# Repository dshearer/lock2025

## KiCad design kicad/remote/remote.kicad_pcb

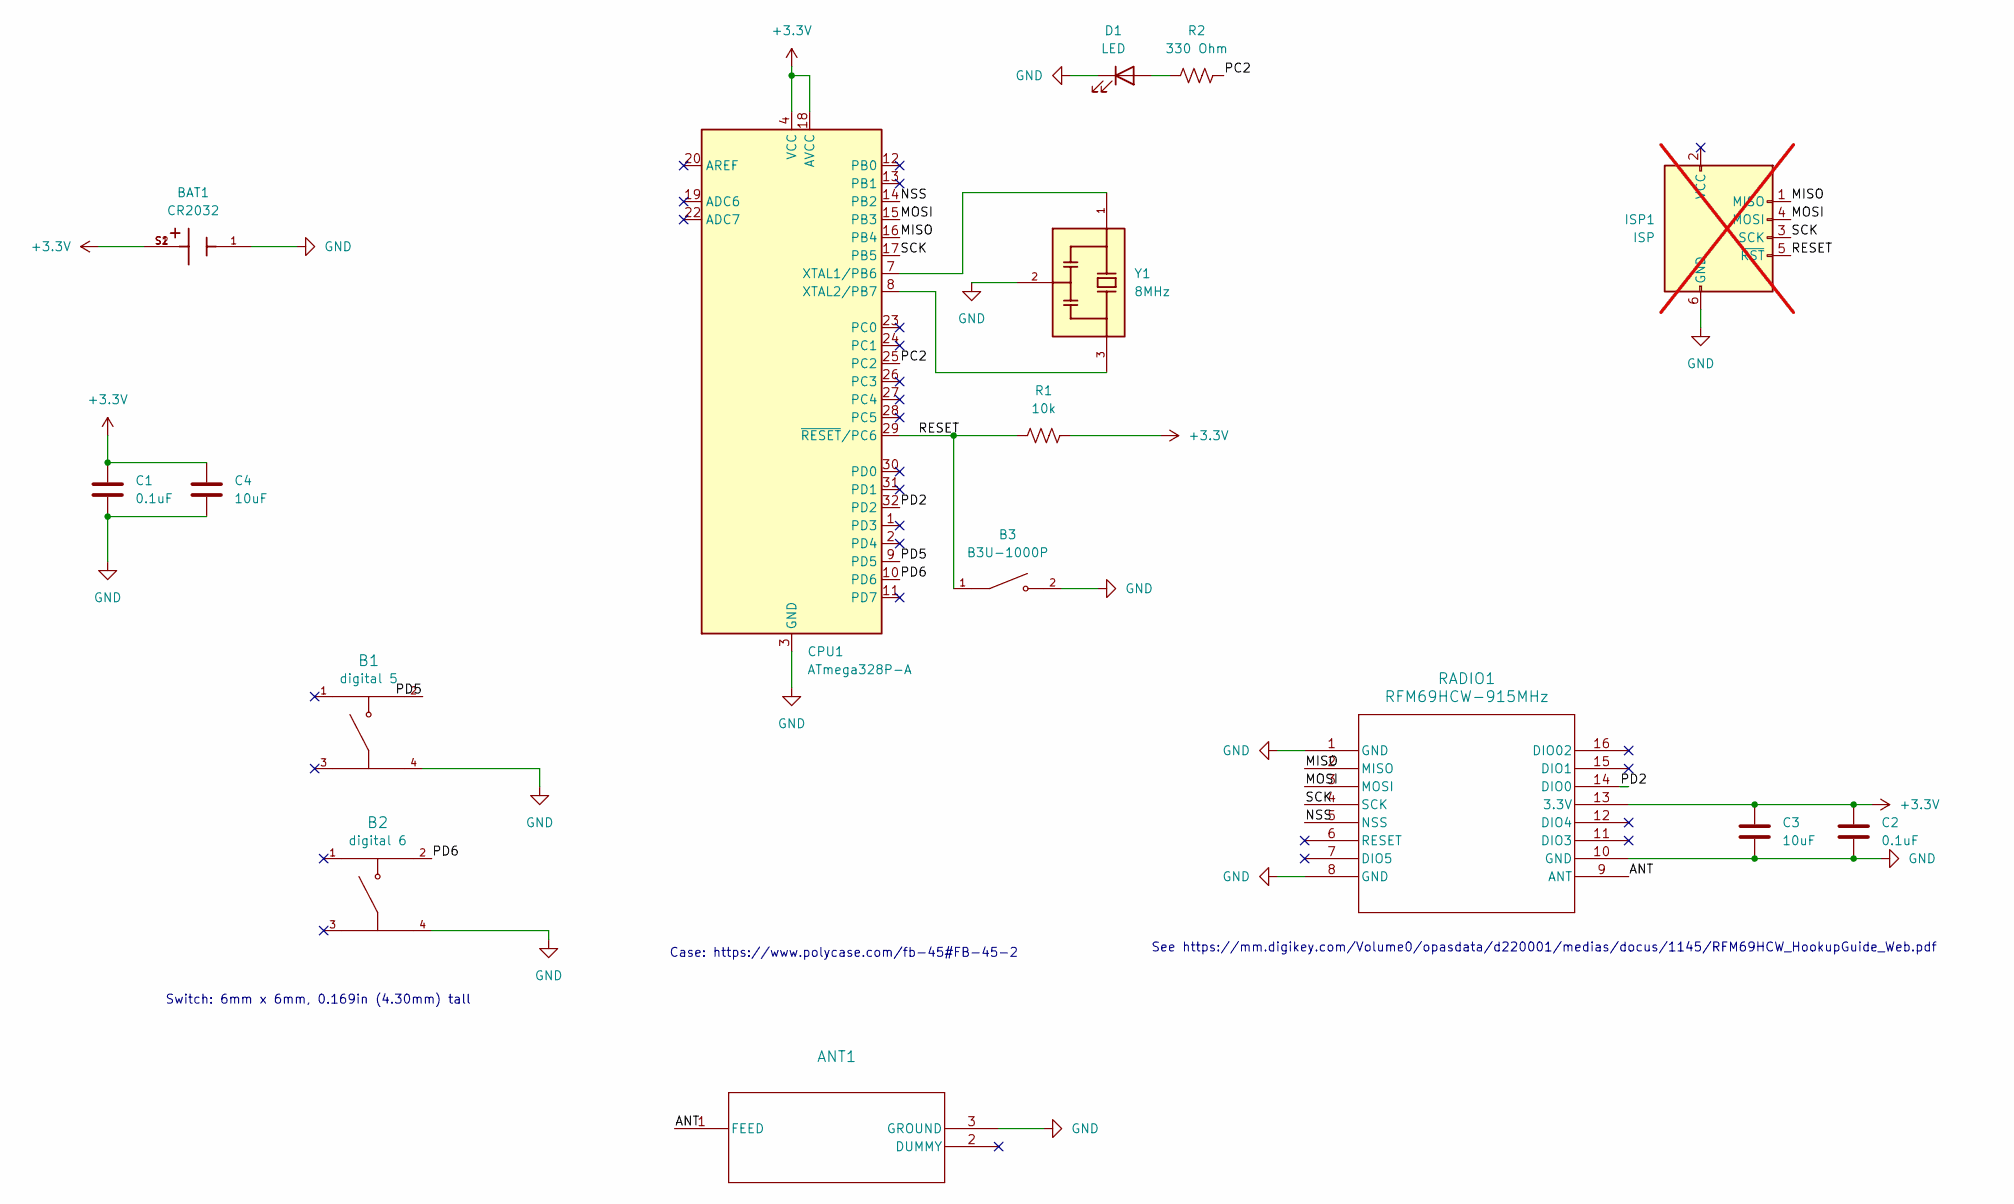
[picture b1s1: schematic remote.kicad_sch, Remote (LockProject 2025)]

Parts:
ANT1: ANTENNA_M620720_KYO; DigiKey part # 478-M620720TR-ND
B1: digital 5; SW_PTS645SK43SMTR92LFS; PARTREV 14 Apr 22; DigiKey part # SW400-ND
B2: digital 6; SW_PTS645SK43SMTR92LFS; PARTREV 14 Apr 22; DigiKey part # SW400-ND
B3: B3U-1000P; BUTTON_SW_B3U-1000P; DigiKey part # SW1020TR-ND
BAT1: CR2032; BAT_BK-912; DigiKey part # BK-912-ND
C1, C2: 0.1uF; C_0805_2012Metric
C3, C4: 10uF; C_0805_2012Metric
CPU1: ATmega328P-A; TQFP-32_7x7mm_P0.8mm; DigiKey part # ATMEGA328P-AURTR-ND
D1: LED; LED_0603_1608Metric
ISP1: ISP; PinSocket_2x03_P2.54mm_Vertical; not fitted
R1: 10k; R_0603_1608Metric
R2: 330 Ohm; R_0603_1608Metric
RADIO1: RFM69HCW-915MHz; RFM69HCW_SPK; DigiKey part # 1568-13909-ND
Y1: 8MHz; CSTNE8M00G550000R0

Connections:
+3.3V: BAT1.S1, BAT1.S2, C1.1, C2.1, C3.1, C4.1, CPU1.4 (VCC), CPU1.6 (VCC), CPU1.18 (AVCC), R1.1, RADIO1.13 (3.3V)
/ANT: ANT1.1 (FEED), RADIO1.9 (ANT)
/MISO: CPU1.16 (PB4), ISP1.1 (MISO), RADIO1.2 (MISO)
/MOSI: CPU1.15 (PB3), ISP1.4 (MOSI), RADIO1.3 (MOSI)
/NSS: CPU1.14 (PB2), RADIO1.5 (NSS)
/PC2: CPU1.25 (PC2), R2.2
/PD2: CPU1.32 (PD2), RADIO1.14 (DIO0)
/PD5: B1.2, CPU1.9 (PD5)
/PD6: B2.2, CPU1.10 (PD6)
/RESET: B3.1, CPU1.29 (~RESET/PC6), ISP1.5 (~RST), R1.2
/SCK: CPU1.17 (PB5), ISP1.3 (SCK), RADIO1.4 (SCK)
GND: ANT1.3 (GROUND), B1.4, B2.4, B3.2, BAT1.1, C1.2, C2.2, C3.2, C4.2, CPU1.3 (GND), CPU1.5 (GND), CPU1.21 (GND), D1.1 (K), ISP1.6 (GND), RADIO1.1 (GND), RADIO1.8 (GND), RADIO1.10 (GND), Y1.2
unnamed: CPU1.7 (XTAL1/PB6), Y1.1
unnamed: CPU1.8 (XTAL2/PB7), Y1.3
unnamed: D1.2 (A), R2.1

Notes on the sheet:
Switch: 6mm x 6mm, 0.169in (4.30mm) tall
See https://mm.digikey.com/Volume0/opasdata/d220001/medias/docus/1145/RFM69HCW_HookupGuide_Web.pdf
Case: https://www.polycase.com/fb-45#FB-45-2

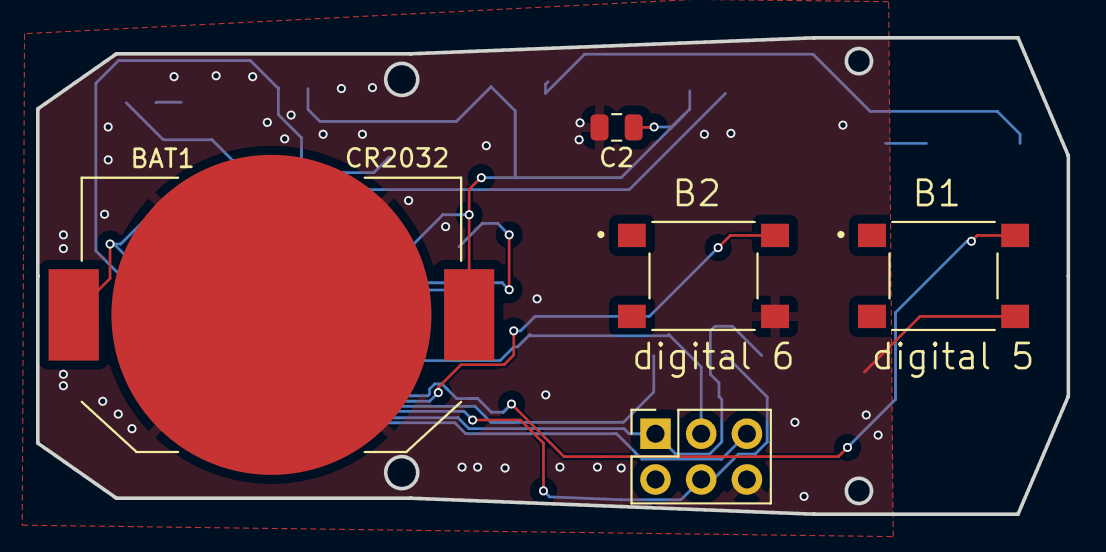
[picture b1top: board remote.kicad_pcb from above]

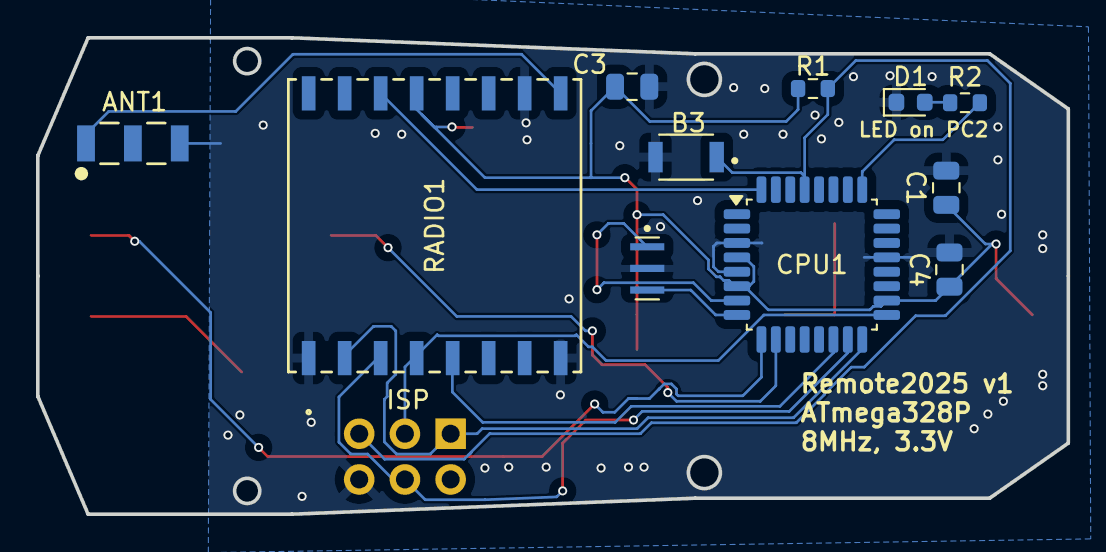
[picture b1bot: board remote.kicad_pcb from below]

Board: 2 copper layers, 57.3 x 26.5 mm, 16 parts (11 on the bottom side), 15 nets.

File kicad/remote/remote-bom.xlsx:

|  |  | Bill of Materials
Item # | *Designator | *Qty | Manufacturer | *Mfg Part # | Description / Value | *Package/Footprint | Type | Your Instructions / Notes
1 | Y1 | 1 |  |  | Three-pin ceramic resonator, 8MHz | 3Pin_7.2x3.0mm | SMD
2 | R1 | 1 |  |  | 10 kOhm resistor | 0603 | SMD
3 | C3,C4 | 2 |  |  | 10 uF capacitor | 0805 | SMD
4 | C1,C2 | 2 |  |  | 0.1 uF capacitor | 0805 | SMD
5 | BAT1 | 1 | MPD (Memory Protection Devices) | BK-912 | Battery Retainer Coin, 20.0mm 1 Cell SMD (SMT) Tab |  | SMD
6 | B3 | 1 | Omron | B3U-1000P | SPST-NO Tactile switch |  | SMD
7 | B2,B1 | 2 | CnK | PTS645SK43SMTR92 LFS | SPST-NO Tactile switch |  | PTH
8 | ANT1 | 1 | Kyocera AVX | M620720 | Ceramic antenna |  | SMD
9 | RADIO1 | 1 | Hoperf | RFM69HCW | General ISM radio IC, 915MHz |  | SMD | 915MHz please! DigiKey has this thing listed with SparkFun as the manufacturer,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
10 | CPU1 | 1 | Microchip | ATMEGA328P-AUR |  | TQFP-32 | SMD
11 | D1 | 1 |  |  | LED (any color) | 0603 | SMD
12 | R2 | 1 |  |  | 330 Ohm | 0603 | SMD

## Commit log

2025-06-28 Moves back and forth!
2025-06-29 use interrupts to read buttons
2025-06-29 Don't move if both buttons pressed
2025-06-29 sleepy sleep
2025-06-29 minor cleanup
2025-07-24 Work with Feather
2025-07-24 Support getting commands from buttons
2025-07-24 High-level actions
2025-07-24 Separate src dirs
2025-07-25 Support single button
2025-07-25 Re-activate idle.cpp
2025-07-25 Go to center after turning
2025-07-26 Script for auto choosing USB port
2025-07-26 led library
2025-07-26 Hardcode monitor ports
2025-07-27 Lock & remote exchange messages
2025-07-27 Change naming in err lib
2025-07-27 Handle too-far sensor failure
2025-08-03 KiCAD project for remote
2025-08-03 kicad remote: add dxf files
2025-08-09 KiCAD project: final design for remote
2025-08-17 platformio.ini: Settings for using custom remote board
    Sets fuses and enables upload without bootloader.
2025-08-17 Revisted remote board design
2025-08-19 kicad: Fix resistor value on remote
2025-08-23 Make led namespace class-based
2025-08-23 Add class for mon LEDs
2025-08-26 Various fixes
    - Make remote work with radio
    - Fixes to lock code
2025-08-26 Doc comments; rename one func
2025-08-27 Add timer module
2025-08-29 Nudge the gear after a turn so that the button doesn't push it back
2025-08-29 Sleep in goToCenter
2025-08-30 Remove prints
2025-08-30 Timer class
2025-09-09 Add notes
2025-09-14 Add some notes
2025-09-14 Remote works with Feather M0
2025-09-14 Revert "Timer class"
    This reverts commit 80a688eb6b004be4d2133dc4a99d0b60d425d5e8.
2025-09-16 lock: Simplify motor stuff
2025-09-17 Cleanup in motor.h/cpp
2025-09-19 Print statement for gear timeout
2025-09-25 tweaks
2025-10-03 Add driver for TB6612FNG
2025-10-05 Remove timer
    Not needed. I'll just do busy-wait.
2025-10-18 current module; stall detector
2025-10-18 hooks.py: Changed boards
2025-10-19 Adjust stall detector
2025-10-19 More notes
2025-10-28 Initial plan
2026-01-09 Initial OpenSpec context
2026-01-09 Add remote spec
